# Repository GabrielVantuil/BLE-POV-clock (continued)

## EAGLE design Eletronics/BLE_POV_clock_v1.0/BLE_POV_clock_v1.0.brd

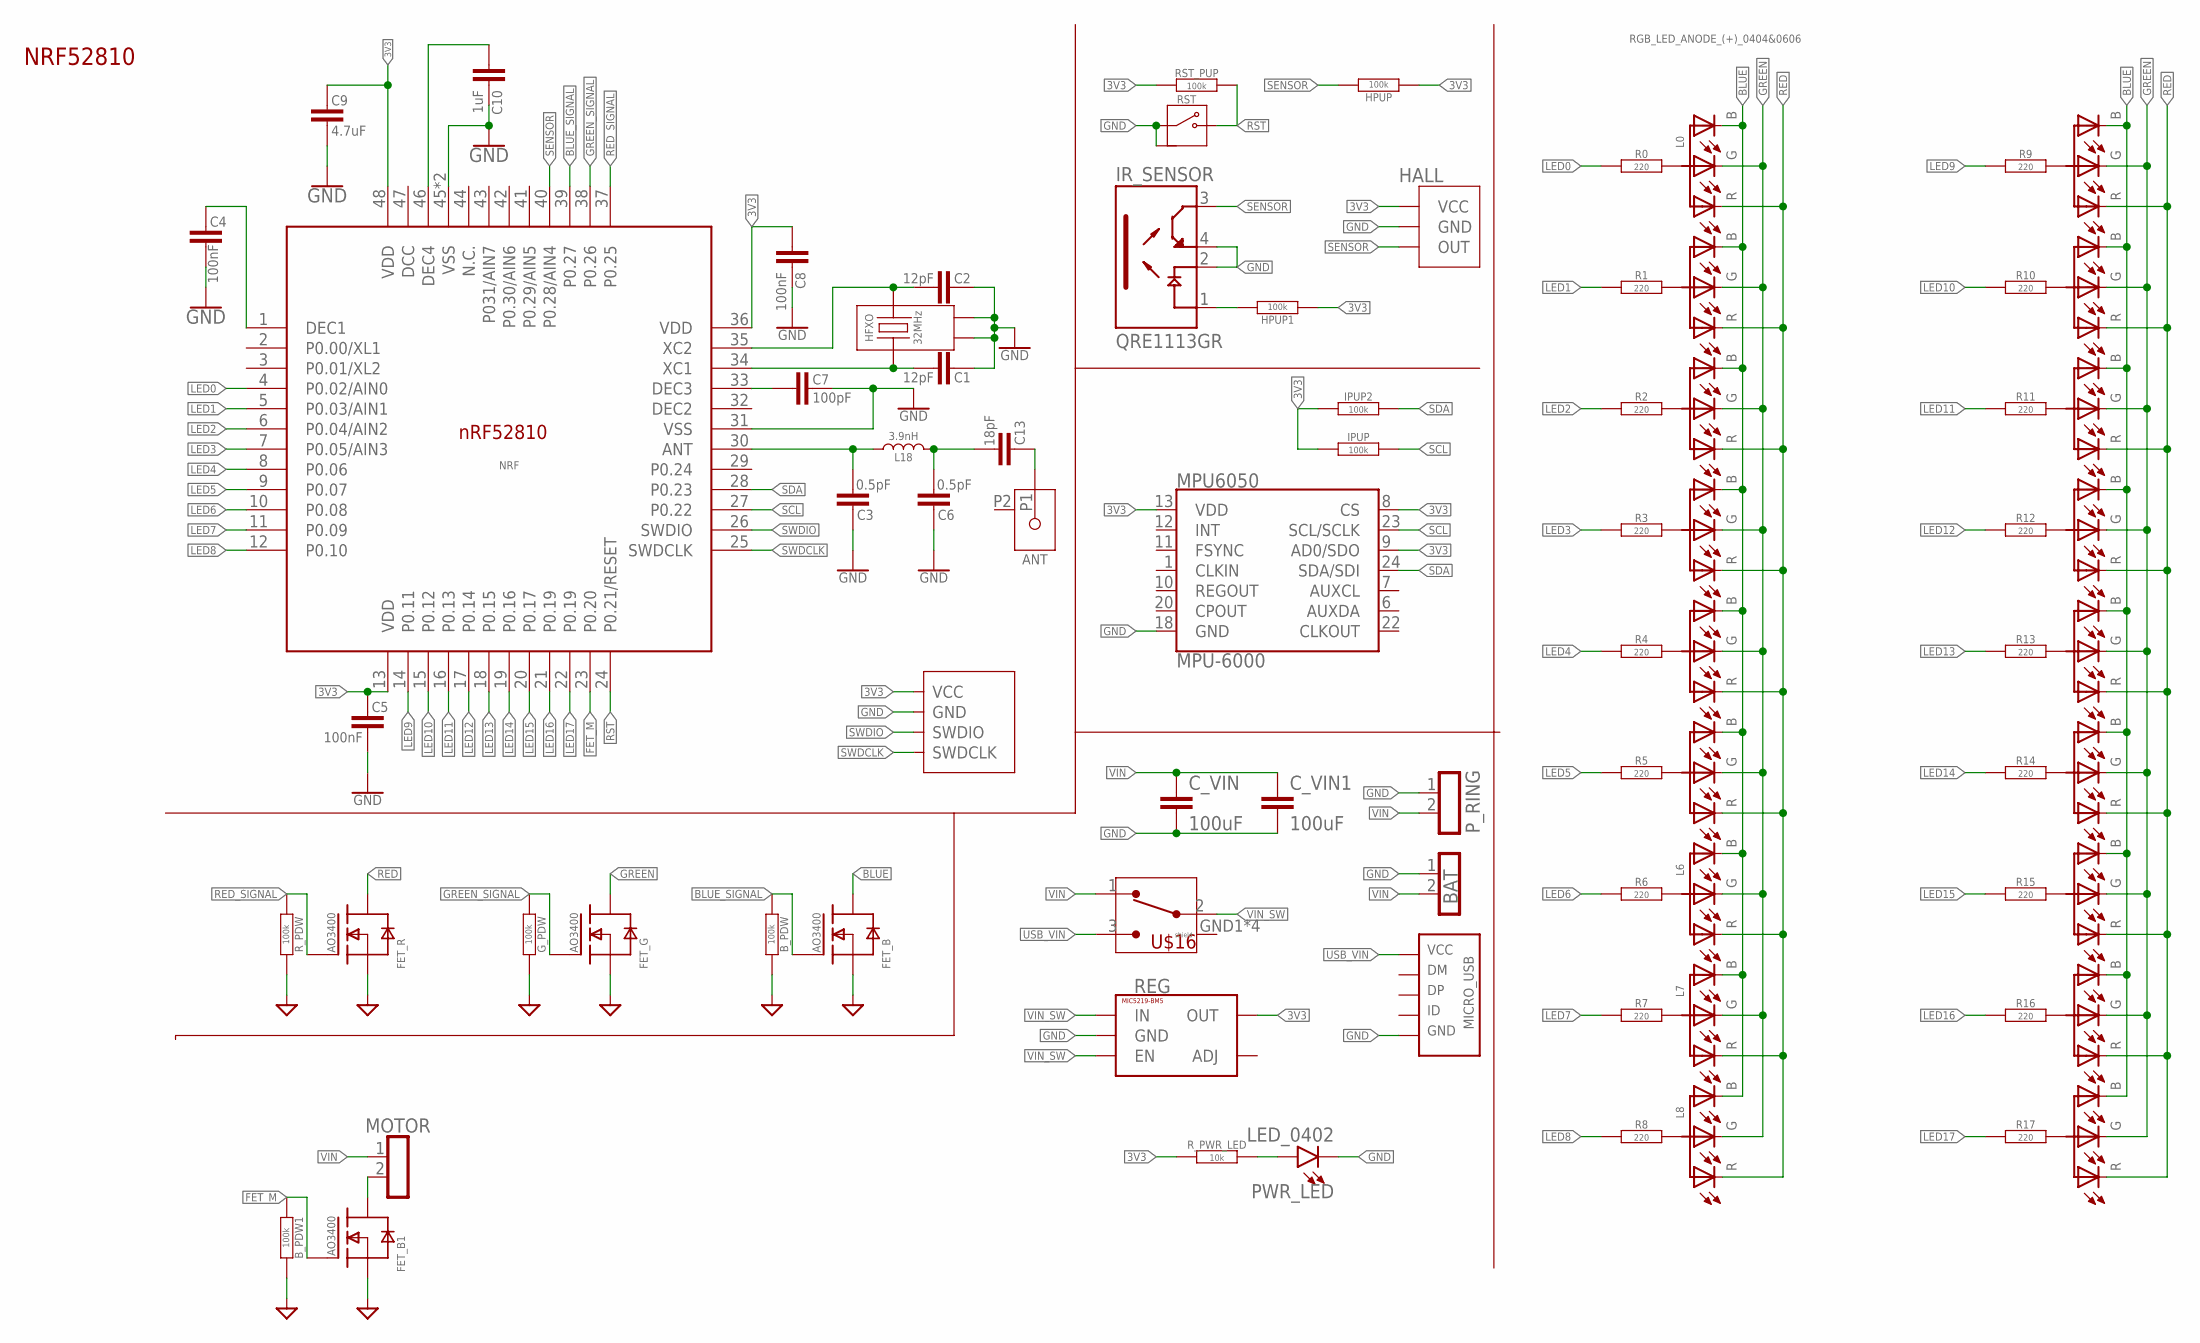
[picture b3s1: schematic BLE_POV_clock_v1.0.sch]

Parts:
ANT: ANT3216LL00R2400A
BAT: PINH1X02; 1X02
B_PDW, B_PDW1: 100k; 0402-RES
C1, C2: 12pF; 0402-CAP
C3, C6: 0.5pF; 0402-CAP
C4, C5, C8: 100nF; 0402-CAP
C7: 100pF; 0402-CAP
C9: 4.7uF; 1206
C10: 1uF; 0402-CAP
C13: 18pF; 0402-CAP
C_VIN, C_VIN1: 100uF; 1206
FET_B, FET_B1: AO3400; SOT23-3
FET_G: AO3400; SOT23-3
FET_R: AO3400; SOT23-3
G_PDW: 100k; 0402-RES
HALL: 49E; TO92_HALLSENSOR
HFXO: 32MHz; XTAL_CX2016DB16000D0WZRC1
HPUP, HPUP1: 100k; 0402-RES
IPUP, IPUP2: 100k; 0402-RES
IR_SENSOR: QRE1113GR; SOIC180P460X187-4N
L0, L1, L2, L3, L4, L5, L6, L7, L8, L9, L10, L11, L12, L13, L14, L15, L16, L17: RGB_LED_ANODE_(+)_0404&0606; LED_RGB_0404&0606
L18: 3.9nH; 0402
MICRO_USB: USBSMALLGND; MICROUSB_SMALLGND
MOTOR: PINH1X02_1.27; 1X02_1.27
MPU6050: MPU-6000; QFN-24-EP
NRF: NORDIC_NRF_NRF52810_QF; NRF52810_QFN40P600X600X90-48_N_3MMTHERMAL
PWR_LED: LED_0402; 0402
P_RING: RING_PAD_2_4X6; 2X_RING_PAD_4X6
R0, R1, R2, R3, R4, R5, R6, R7, R8, R9, R10, R11, R12, R13, R14, R15, R16, R17: 220; 0402-RES
REG: MIC5219-BM5; SOT23-5
RST: PUSHBUTTON_2X4X3.5; 2X4X3.5MM
RST_PUP: 100k; 0402-RES
R_PDW: 100k; 0402-RES
R_PWR_LED: 10k; 0402-RES
U$2: GV_SWD_4P; GV_SWD_1.27MM_4P_SEMI_SMD
U$16: SMD_SWITCH

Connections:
3V3: C5.1, C8.2, C9.1, HALL.VCC, HPUP.1, HPUP1.1, IPUP.1, IPUP2.1, MPU6050.8 (CS), MPU6050.9 (AD0/SDO), MPU6050.13 (VDD), NRF.13 (VDD), NRF.36 (VDD), NRF.48 (VDD), REG.5 (OUT), RST_PUP.1, R_PWR_LED.1, U$2.VCC
BLUE: FET_B.3 (D), L0.B (LED_BLUE), L0.B1 (LED_BLUE), L1.B (LED_BLUE), L1.B1 (LED_BLUE), L2.B (LED_BLUE), L2.B1 (LED_BLUE), L3.B (LED_BLUE), L3.B1 (LED_BLUE), L4.B (LED_BLUE), L4.B1 (LED_BLUE), L5.B (LED_BLUE), L5.B1 (LED_BLUE), L6.B (LED_BLUE), L6.B1 (LED_BLUE), L7.B (LED_BLUE), L7.B1 (LED_BLUE), L8.B (LED_BLUE), L8.B1 (LED_BLUE), L9.B (LED_BLUE), L9.B1 (LED_BLUE), L10.B (LED_BLUE), L10.B1 (LED_BLUE), L11.B (LED_BLUE), L11.B1 (LED_BLUE), L12.B (LED_BLUE), L12.B1 (LED_BLUE), L13.B (LED_BLUE), L13.B1 (LED_BLUE), L14.B (LED_BLUE), L14.B1 (LED_BLUE), L15.B (LED_BLUE), L15.B1 (LED_BLUE), L16.B (LED_BLUE), L16.B1 (LED_BLUE), L17.B (LED_BLUE), L17.B1 (LED_BLUE)
BLUE_SIGNAL: B_PDW.1, FET_B.1 (G), NRF.39 (P0.27)
FET_M: B_PDW1.1, FET_B1.1 (G), NRF.23 (P0.20)
GND: BAT.1, B_PDW.2, B_PDW1.2, C1.1, C2.1, C3.2, C4.2, C5.2, C6.2, C7.1, C8.1, C9.2, C10.1, C_VIN.2, C_VIN1.2, FET_B.2 (S), FET_B1.2 (S), FET_G.2 (S), FET_R.2 (S), G_PDW.2, HALL.GND, HFXO.2, HFXO.4, IR_SENSOR.2 (C), IR_SENSOR.4 (ET), MICRO_USB.5 (5.GND), MICRO_USB.5.GND1 (5.GND), MICRO_USB.5.GND4 (5.GND), MPU6050.18 (GND), NRF.31 (VSS), NRF.45 (VSS), NRF.PAD (VSS), PWR_LED.C, P_RING.1, REG.2 (GND), RST.2, RST.GND, RST.GND2 (GND), R_PDW.2, U$2.GND
GREEN: FET_G.3 (D), L0.G (LED_GREEN), L0.G1 (LED_GREEN), L1.G (LED_GREEN), L1.G1 (LED_GREEN), L2.G (LED_GREEN), L2.G1 (LED_GREEN), L3.G (LED_GREEN), L3.G1 (LED_GREEN), L4.G (LED_GREEN), L4.G1 (LED_GREEN), L5.G (LED_GREEN), L5.G1 (LED_GREEN), L6.G (LED_GREEN), L6.G1 (LED_GREEN), L7.G (LED_GREEN), L7.G1 (LED_GREEN), L8.G (LED_GREEN), L8.G1 (LED_GREEN), L9.G (LED_GREEN), L9.G1 (LED_GREEN), L10.G (LED_GREEN), L10.G1 (LED_GREEN), L11.G (LED_GREEN), L11.G1 (LED_GREEN), L12.G (LED_GREEN), L12.G1 (LED_GREEN), L13.G (LED_GREEN), L13.G1 (LED_GREEN), L14.G (LED_GREEN), L14.G1 (LED_GREEN), L15.G (LED_GREEN), L15.G1 (LED_GREEN), L16.G (LED_GREEN), L16.G1 (LED_GREEN), L17.G (LED_GREEN), L17.G1 (LED_GREEN)
GREEN_SIGNAL: FET_G.1 (G), G_PDW.1, NRF.38 (P0.26)
LED0: NRF.4 (P0.02/AIN0), R0.1
LED1: NRF.5 (P0.03/AIN1), R1.1
LED2: NRF.6 (P0.04/AIN2), R2.1
LED3: NRF.7 (P0.05/AIN3), R3.1
LED4: NRF.8 (P0.06), R4.1
LED5: NRF.9 (P0.07), R5.1
LED6: NRF.10 (P0.08), R6.1
LED7: NRF.11 (P0.09), R7.1
LED8: NRF.12 (P0.10), R8.1
LED9: NRF.14 (P0.11), R9.1
LED10: NRF.15 (P0.12), R10.1
LED11: NRF.16 (P0.13), R11.1
LED12: NRF.17 (P0.14), R12.1
LED13: NRF.18 (P0.15), R13.1
LED14: NRF.19 (P0.16), R14.1
LED15: NRF.20 (P0.17), R15.1
LED16: NRF.21 (P0.19), R16.1
LED17: NRF.22 (P0.19), R17.1
MOTOR: FET_B1.3 (D), MOTOR.2
unnamed: C1.2, HFXO.3, NRF.34 (XC1)
unnamed: C2.2, HFXO.1, NRF.35 (XC2)
unnamed: C7.2, NRF.33 (DEC3)
unnamed: L0.COM (COMMON_ANODE), L0.COM1 (COMMON_ANODE), R0.2
unnamed: L1.COM (COMMON_ANODE), L1.COM1 (COMMON_ANODE), R1.2
unnamed: L2.COM (COMMON_ANODE), L2.COM1 (COMMON_ANODE), R2.2
unnamed: L3.COM (COMMON_ANODE), L3.COM1 (COMMON_ANODE), R3.2
unnamed: C10.2, NRF.46 (DEC4)
unnamed: C3.1, L18.1, NRF.30 (ANT)
unnamed: C4.1, NRF.1 (DEC1)
unnamed: HPUP1.2, IR_SENSOR.1 (A)
unnamed: L4.COM (COMMON_ANODE), L4.COM1 (COMMON_ANODE), R4.2
unnamed: L5.COM (COMMON_ANODE), L5.COM1 (COMMON_ANODE), R5.2
unnamed: L6.COM (COMMON_ANODE), L6.COM1 (COMMON_ANODE), R6.2
unnamed: L7.COM (COMMON_ANODE), L7.COM1 (COMMON_ANODE), R7.2
unnamed: C6.1, C13.1, L18.2
unnamed: ANT.P1, C13.2
unnamed: L8.COM (COMMON_ANODE), L8.COM1 (COMMON_ANODE), R8.2
unnamed: L9.COM (COMMON_ANODE), L9.COM1 (COMMON_ANODE), R9.2
unnamed: L10.COM (COMMON_ANODE), L10.COM1 (COMMON_ANODE), R10.2
unnamed: L11.COM (COMMON_ANODE), L11.COM1 (COMMON_ANODE), R11.2
unnamed: L12.COM (COMMON_ANODE), L12.COM1 (COMMON_ANODE), R12.2
unnamed: L13.COM (COMMON_ANODE), L13.COM1 (COMMON_ANODE), R13.2
unnamed: L14.COM (COMMON_ANODE), L14.COM1 (COMMON_ANODE), R14.2
unnamed: L15.COM (COMMON_ANODE), L15.COM1 (COMMON_ANODE), R15.2
unnamed: L16.COM (COMMON_ANODE), L16.COM1 (COMMON_ANODE), R16.2
unnamed: L17.COM (COMMON_ANODE), L17.COM1 (COMMON_ANODE), R17.2
unnamed: PWR_LED.A, R_PWR_LED.2
RED: FET_R.3 (D), L0.R (LED_RED), L0.R1 (LED_RED), L1.R (LED_RED), L1.R1 (LED_RED), L2.R (LED_RED), L2.R1 (LED_RED), L3.R (LED_RED), L3.R1 (LED_RED), L4.R (LED_RED), L4.R1 (LED_RED), L5.R (LED_RED), L5.R1 (LED_RED), L6.R (LED_RED), L6.R1 (LED_RED), L7.R (LED_RED), L7.R1 (LED_RED), L8.R (LED_RED), L8.R1 (LED_RED), L9.R (LED_RED), L9.R1 (LED_RED), L10.R (LED_RED), L10.R1 (LED_RED), L11.R (LED_RED), L11.R1 (LED_RED), L12.R (LED_RED), L12.R1 (LED_RED), L13.R (LED_RED), L13.R1 (LED_RED), L14.R (LED_RED), L14.R1 (LED_RED), L15.R (LED_RED), L15.R1 (LED_RED), L16.R (LED_RED), L16.R1 (LED_RED), L17.R (LED_RED), L17.R1 (LED_RED)
RED_SIGNAL: FET_R.1 (G), NRF.37 (P0.25), R_PDW.1
RST: NRF.24 (P0.21/RESET), RST.1, RST_PUP.2
SCL: IPUP.2, MPU6050.23 (SCL/SCLK), NRF.27 (P0.22)
SDA: IPUP2.2, MPU6050.24 (SDA/SDI), NRF.28 (P0.23)
SENSOR: HALL.OUT, HPUP.2, IR_SENSOR.3 (CT), NRF.40 (P0.28/AIN4)
SWDCLK: NRF.25 (SWDCLK), U$2.SWDCLK
SWDIO: NRF.26 (SWDIO), U$2.SWDIO
USB_VIN: MICRO_USB.1 (1.VCC), U$16.3
VIN: BAT.2, C_VIN.1, C_VIN1.1, MOTOR.1, P_RING.2, U$16.1
VIN_SW: REG.1 (IN), REG.3 (EN), U$16.2

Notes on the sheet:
NRF52810

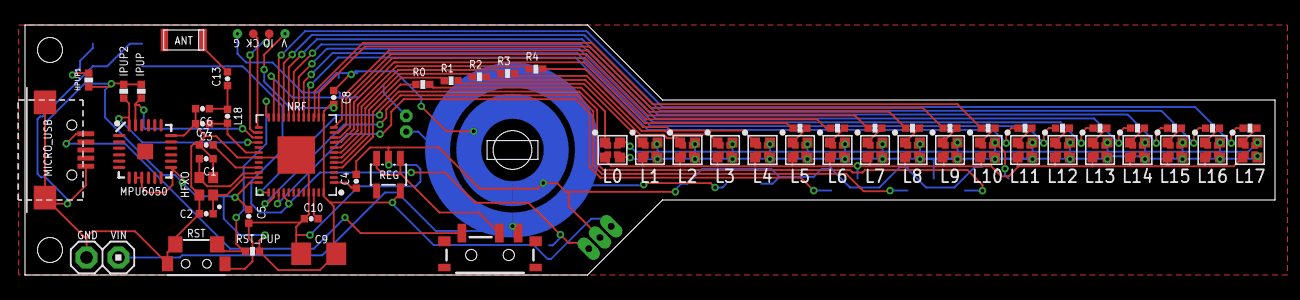
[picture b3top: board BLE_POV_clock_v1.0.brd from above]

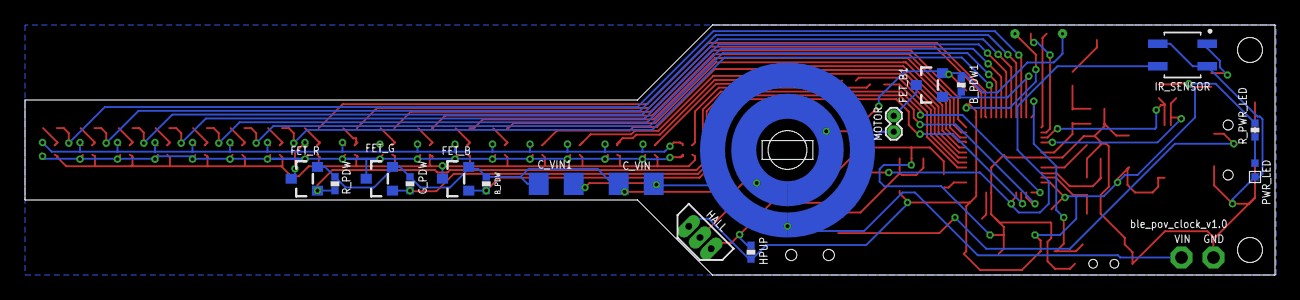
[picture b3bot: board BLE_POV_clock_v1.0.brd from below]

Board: 2 copper layers, 100.0 x 20.0 mm, 80 parts (18 on the bottom side), 65 nets.

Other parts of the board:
U$7: GV_5MM_METAL

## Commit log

2024-05-19 Added board BLE_POV_clock_v1.0
2024-05-20 Code basics: writting text functions, font 7 px A-Z ready, only few letters of font 16 px ready.
    Simple coloring texts.
    No pwm used yet.
    No BLE code.
2024-06-01 BLE_POV_clock_v2.0:
    - More leds (44 total);
    - Rectangular pcb, with 150mm;
    - Battery charger, with 2477 battery holder;
2024-08-30 BLE_POV_clock_v2.0 final version
2024-08-30 Adding code to draw colored images, text and other (v1 board)
2024-09-03 Simple tests for the v2 board and 32x32 pixels images
2024-09-29 Adding simple button press behavior and inversion of full line
2024-12-31 Updated "write_text" to work on the v2.0 board. Added bluetooth support (incomplete but the basics is functional)
2025-01-03 CAD: board holder + base
2025-01-03 Adding first tests of motor controlling (only on-off)
2025-01-04 Added syncronization by hall sensor and gpio interrupt
2025-01-05 Added PWM at control motor
2025-01-07 Increased performance, pixels now can be smaller
2025-01-12 Now it can receive more data from phone, so all 3 current modes work
2025-01-13 Added syncronization
2025-01-14 Changing set led functions
2025-01-14 Refactoring
2025-01-28 BLE_POV_Display_v2.1 (rename):
    - Motor onboard;
    - Battery voltage measurement (experimental, through a trick using mosfets and the tristate pin);
    - Changed to 2 LIR2450 batteries (also used as counterweight);
    - All the positioning was made considering the weights, so that (hopefully) is all balanced ;
2025-10-26 Small updated related to the new version
